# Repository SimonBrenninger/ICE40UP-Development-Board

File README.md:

# ICE40UP Development Board

is a small formfactor, entry-level FPGA development board using a Lattice Semiconductor ultra low power chip.

## ICE40UP Features

## Board Features

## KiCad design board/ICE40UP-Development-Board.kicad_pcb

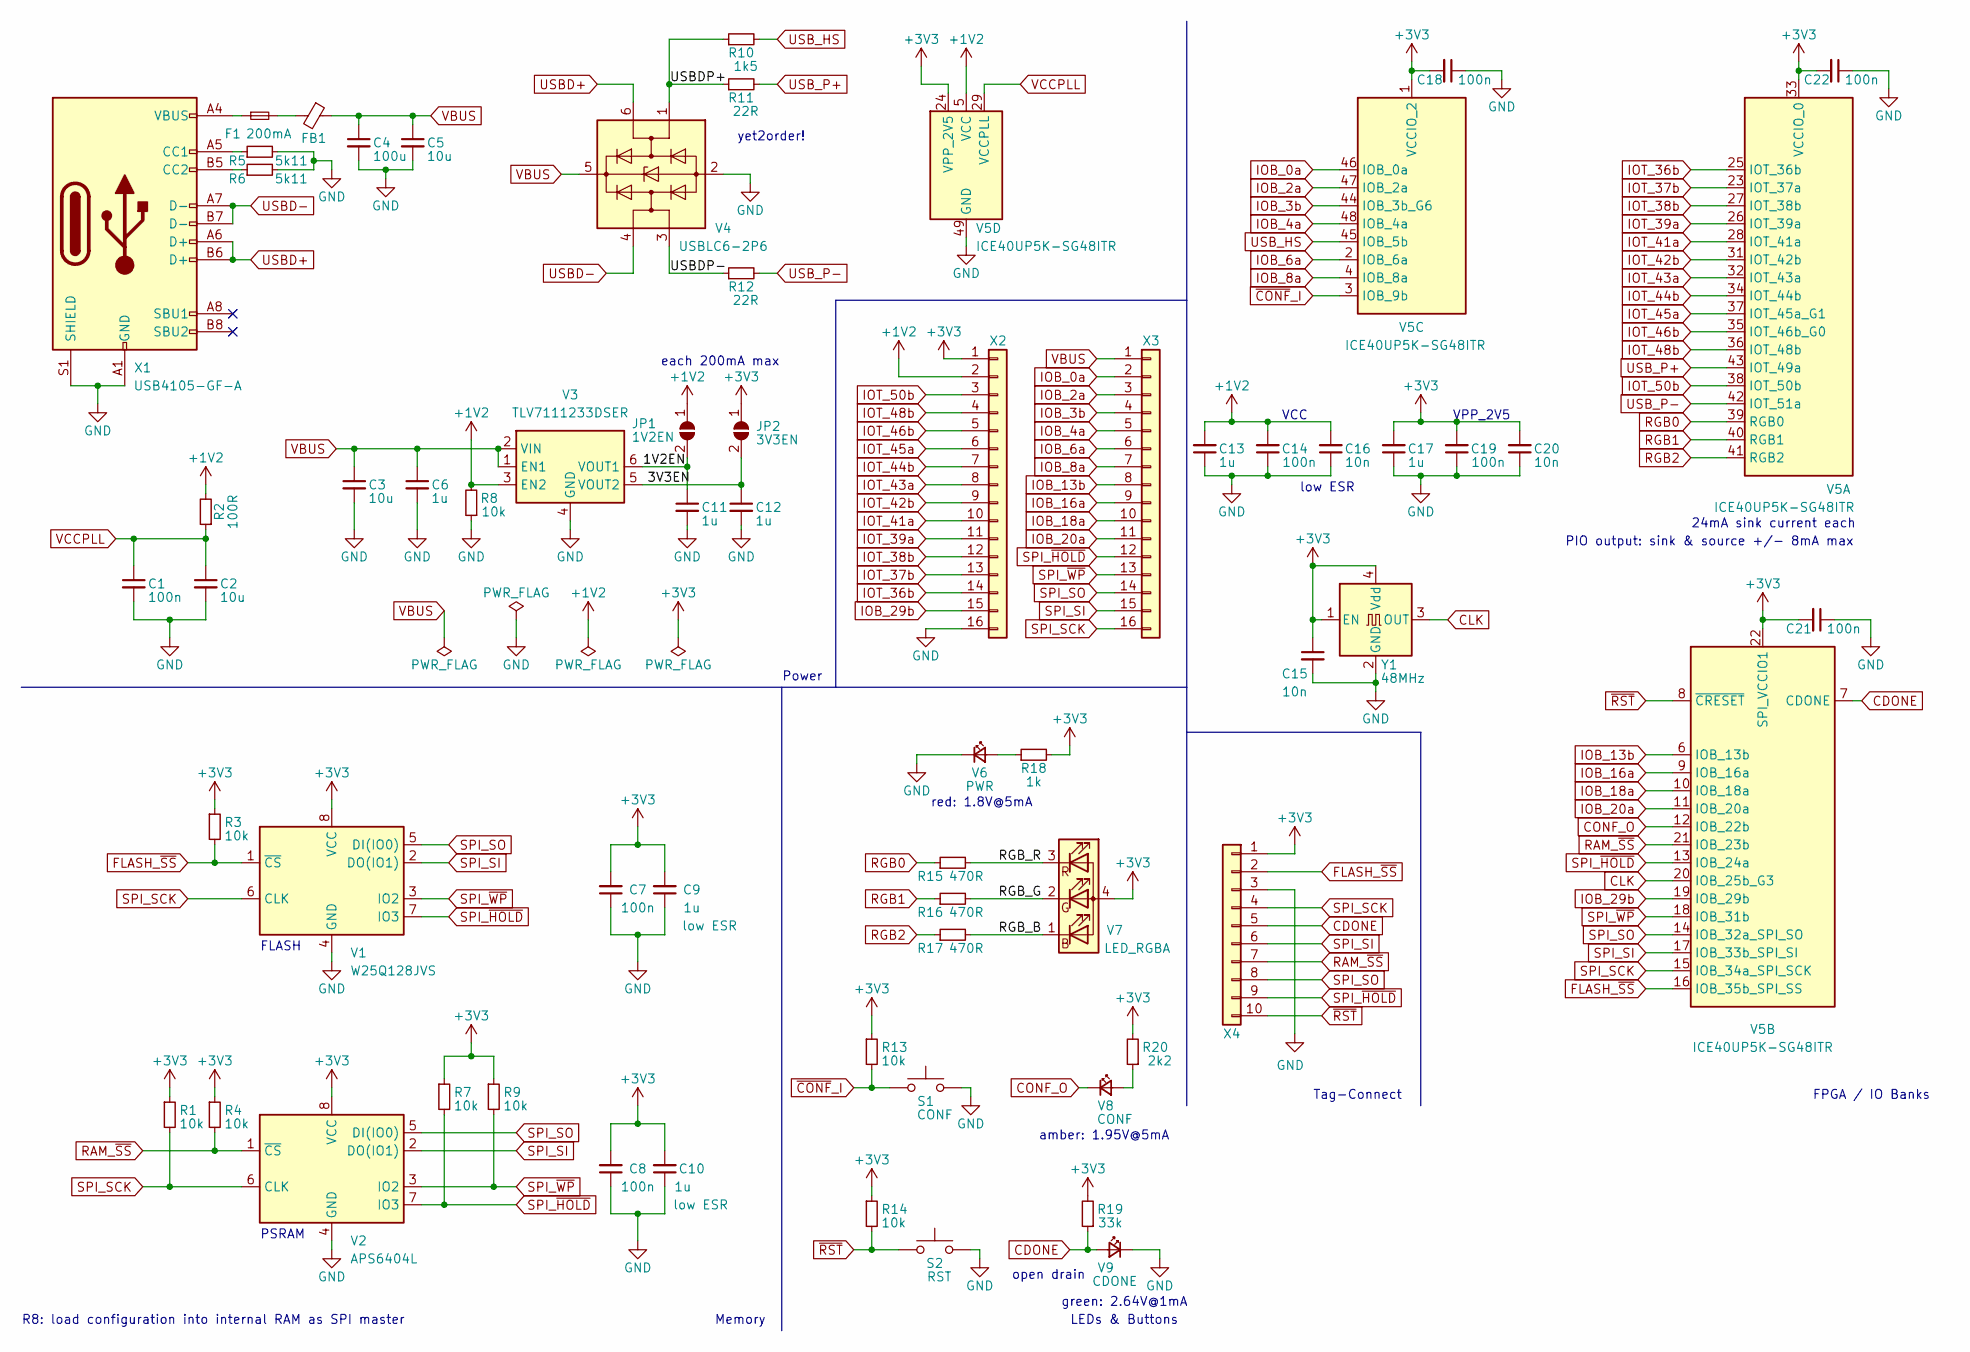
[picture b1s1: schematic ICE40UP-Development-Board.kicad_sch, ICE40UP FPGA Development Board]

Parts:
C1, C7, C8, C14, C18, C19, C21, C22: 100n; C_0402_1005Metric
C2, C3, C5: 10u; C_0402_1005Metric
C4: 100u; C_0805_2012Metric
C6, C9, C10, C11, C12, C13, C17: 1u; C_0402_1005Metric
C15, C16, C20: 10n; C_0402_1005Metric
F1: 200mA; Fuse_0805_2012Metric
FB1: FerriteBead_Small; L_0603_1608Metric
JP1: 1V2EN; SolderJumper-2_P1.3mm_Open_RoundedPad1.0x1.5mm
JP2: 3V3EN; SolderJumper-2_P1.3mm_Open_RoundedPad1.0x1.5mm
R1, R3, R4, R7, R8, R9, R13, R14: 10k; R_0402_1005Metric
R2: 100R; R_0402_1005Metric
R5, R6: 5k11; R_0402_1005Metric
R10: 1k5; R_0402_1005Metric
R11, R12: 22R; R_0402_1005Metric
R15, R16, R17: 470R; R_0402_1005Metric
R18: 1k; R_0402_1005Metric
R19: 33k; R_0402_1005Metric
R20: 2k2; R_0402_1005Metric
S1: CONF; SW_SPST_EVQP2
S2: RST; SW_SPST_EVQP2
V1: W25Q128JVS; SOIC-8_5.23x5.23mm_P1.27mm
V2: APS6404L; SON-8-1EP_3x2mm_P0.5mm_EP1.4x1.6mm
V3: TLV7111233DSER; WSON-6_1.5x1.5mm_P0.5mm
V4: USBLC6-2P6; SOT-666
V5: ICE40UP5K-SG48ITR; QFN-48-1EP_7x7mm_P0.5mm_EP5.6x5.6mm
V6: PWR; LED_0603_1608Metric
V7: LED_RGBA; CREE_UHD111A
V8: CONF; LED_0603_1608Metric
V9: CDONE; LED_0603_1608Metric
X1: USB4105-GF-A; USB_C_Receptacle_G-Switch_GT-USB-7010ASV
X2, X3: Conn_01x16; PinHeader_1x16_P2.54mm_Vertical
X4: Tag-Connect; Tag-Connect_TC2050-IDC-FP_2x05_P1.27mm_Vertical
Y1: 48MHz; Oscillator_SMD_Abracon_ASE-4Pin_3.2x2.5mm

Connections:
+1V2: C13.2, C14.2, C16.2, JP1.1 (A), R2.2, R8.2, V3.3 (EN2), V5.5 (VCC), V5.30 (VCC), X2.2
+3V3: C7.2, C8.2, C9.2, C10.2, C15.1, C17.2, C18.2, C19.2, C20.2, C21.2, C22.2, JP2.1 (A), R1.1, R3.1, R4.1, R7.1, R9.1, R13.1, R14.1, R18.2, R19.2, R20.2, V1.8 (VCC), V2.8 (VCC), V5.1 (VCCIO_2), V5.22 (SPI_VCCIO1), V5.24 (VPP_2V5), V5.33 (VCCIO_0), V7.4 (A), X2.1, X4.1, Y1.1 (EN), Y1.4 (Vdd)
/1V2EN: C11.1, JP1.2 (B), V3.6 (VOUT1)
/3V3EN: C12.1, JP2.2 (B), V3.5 (VOUT2)
/RGB_B: R17.2, V7.1 (BK)
/RGB_G: R16.2, V7.2 (GK)
/RGB_R: R15.2, V7.3 (RK)
/USBDP+: R10.1, R11.1, V4.1 (I/O1)
/USBDP-: R12.1, V4.3 (I/O2)
CDONE: R19.1, V5.7 (CDONE), V9.2 (A), X4.5
CLK: V5.20 (IOB_25b_G3), Y1.3 (OUT)
CONF_O: V5.12 (IOB_22b), V8.1 (K)
FLASH_~SS: R3.2, V1.1 (~CS), V5.16 (IOB_35b_SPI_SS), X4.2
GND: C1.2, C2.2, C3.2, C4.2, C5.2, C6.2, C7.1, C8.1, C9.1, C10.1, C11.2, C12.2, C13.1, C14.1, C15.2, C16.1, C17.1, C18.1, C19.1, C20.1, C21.1, C22.1, R5.2, R6.2, R8.1, S1.2, S2.2, V1.4 (GND), V2.4 (GND), V3.4 (GND), V4.2 (GND), V5.49 (GND), V6.1 (K), V9.1 (K), X1.A1 (GND), X1.A12 (GND), X1.B1 (GND), X1.B12 (GND), X1.S1 (SHIELD), X2.16, X4.3, Y1.2 (GND)
IOB_0a: V5.46 (IOB_0a), X3.2
IOB_2a: V5.47 (IOB_2a), X3.3
IOB_3b: V5.44 (IOB_3b_G6), X3.4
IOB_4a: V5.48 (IOB_4a), X3.5
IOB_6a: V5.2 (IOB_6a), X3.6
IOB_8a: V5.4 (IOB_8a), X3.7
IOB_13b: V5.6 (IOB_13b), X3.8
IOB_16a: V5.9 (IOB_16a), X3.9
IOB_18a: V5.10 (IOB_18a), X3.10
IOB_20a: V5.11 (IOB_20a), X3.11
IOB_29b: V5.19 (IOB_29b), X2.15
IOT_36b: V5.25 (IOT_36b), X2.14
IOT_37b: V5.23 (IOT_37a), X2.13
IOT_38b: V5.27 (IOT_38b), X2.12
IOT_39a: V5.26 (IOT_39a), X2.11
IOT_41a: V5.28 (IOT_41a), X2.10
IOT_42b: V5.31 (IOT_42b), X2.9
IOT_43a: V5.32 (IOT_43a), X2.8
IOT_44b: V5.34 (IOT_44b), X2.7
IOT_45a: V5.37 (IOT_45a_G1), X2.6
IOT_46b: V5.35 (IOT_46b_G0), X2.5
IOT_48b: V5.36 (IOT_48b), X2.4
IOT_50b: V5.38 (IOT_50b), X2.3
unnamed: F1.1, X1.A4 (VBUS), X1.A9 (VBUS), X1.B4 (VBUS), X1.B9 (VBUS)
unnamed: F1.2, FB1.2
unnamed: R18.1, V6.2 (A)
unnamed: R20.1, V8.2 (A)
unnamed: R5.1, X1.A5 (CC1)
unnamed: R6.1, X1.B5 (CC2)
RAM_~SS: R4.2, V2.1 (~CS), V5.21 (IOB_23b), X4.7
RGB0: R15.1, V5.39 (RGB0)
RGB1: R16.1, V5.40 (RGB1)
RGB2: R17.1, V5.41 (RGB2)
SPI_SCK: R1.2, V1.6 (CLK), V2.6 (CLK), V5.15 (IOB_34a_SPI_SCK), X3.16, X4.4
SPI_SI: V1.2 (DO(IO1)), V2.2 (DO(IO1)), V5.17 (IOB_33b_SPI_SI), X3.15, X4.6
SPI_SO: V1.5 (DI(IO0)), V2.5 (DI(IO0)), V5.14 (IOB_32a_SPI_SO), X3.14, X4.8
SPI_~HOLD: R7.2, V1.7 (IO3), V2.7 (IO3), V5.13 (IOB_24a), X3.12, X4.9
SPI_~WP: R9.2, V1.3 (IO2), V2.3 (IO2), V5.18 (IOB_31b), X3.13
USBD+: V4.6 (I/O1), X1.A6 (D+), X1.B6 (D+)
USBD-: V4.4 (I/O2), X1.A7 (D-), X1.B7 (D-)
USB_HS: R10.2, V5.45 (IOB_5b)
USB_P+: R11.2, V5.43 (IOT_49a)
USB_P-: R12.2, V5.42 (IOT_51a)
VBUS: C3.1, C4.1, C5.1, C6.1, FB1.1, V3.1 (EN1), V3.2 (VIN), V4.5 (VBUS), X3.1
VCCPLL: C1.1, C2.1, R2.1, V5.29 (VCCPLL)
~CONF_I: R13.2, S1.1, V5.3 (IOB_9b)
~RST: R14.2, S2.1, V5.8 (~CRESET), X4.10

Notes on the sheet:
green: 2.64V@1mA
each 200mA max
red: 1.8V@5mA
FPGA / IO Banks
R8: load configuration into internal RAM as SPI master
Memory
Power
open drain
Tag-Connect
amber: 1.95V@5mA
LEDs & Buttons
yet2order!
FLASH
low ESR
PIO output: sink & source +/- 8mA max
VPP_2V5
24mA sink current each
PSRAM
VCC

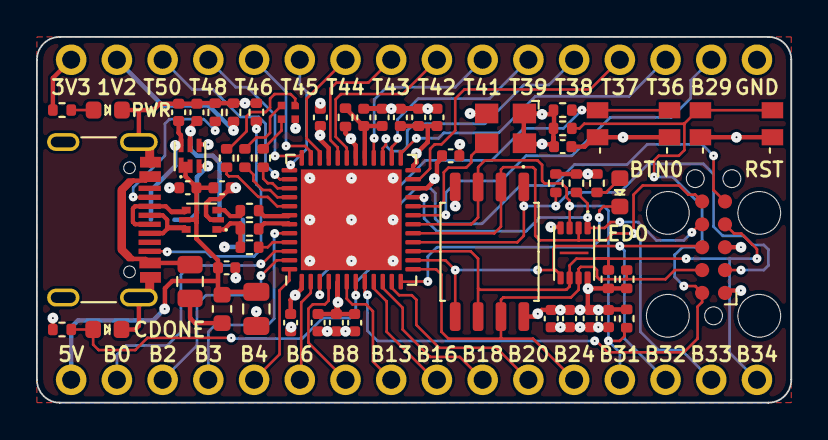
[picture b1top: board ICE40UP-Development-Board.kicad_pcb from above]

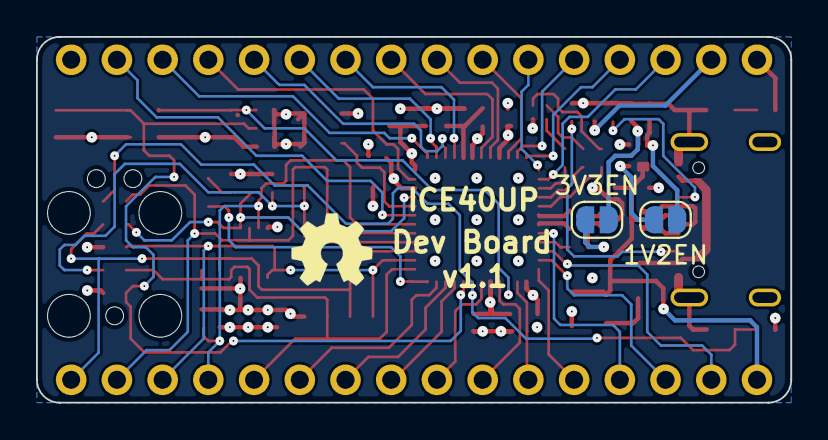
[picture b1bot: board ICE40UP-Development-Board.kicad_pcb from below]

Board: 4 copper layers, 41.9 x 20.3 mm, 62 parts (4 on the bottom side), 61 nets.

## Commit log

2023-03-04 add LICENSE
2023-03-04 add kicad project
2023-03-04 add documentation
2023-03-05 add footprints
2023-03-05 add pcb layout
2023-03-05 import board setup
2023-03-12 change ldo regulator ic
2023-03-12 add bom
2023-03-12 edit README
2023-08-21 finish schematic design
2023-08-21 add datasheets
2023-08-21 start pcb layout; add 3d models
2023-12-28 initial pcb layout
2024-01-03 decrease pcb size; remove SPI-SS signals from breakout pins
2024-01-07 increase size of RAM pads
2024-02-03 change led resistor values
2024-02-05 change tag-connect pinout; add reset signal to tag-connect
2024-02-08 add back silkscreen
2024-02-29 change led resistor values, again
2024-03-11 update rgb led resistors; change capacitor placement
2024-04-03 add QSPI nWP & nHOLD pull-up resistors
